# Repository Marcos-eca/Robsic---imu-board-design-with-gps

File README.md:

# Módulo GPS-IMU.

## Representação 2d e 3d da placa

## Elementos principais para a confecção da placa:

* GPS e IMU - OpenIMU300ZI.
* Esquematico do regulador de tensão fornecido pelo texas instruments no datasheet do LM1117.

## Connector e tabela de informações sobre a função de cada pino do IMU.

## Informações sobre a alimentação, conexão das portas seriais e o seletor de interface (pin_7 - comunicação UART/SPI).

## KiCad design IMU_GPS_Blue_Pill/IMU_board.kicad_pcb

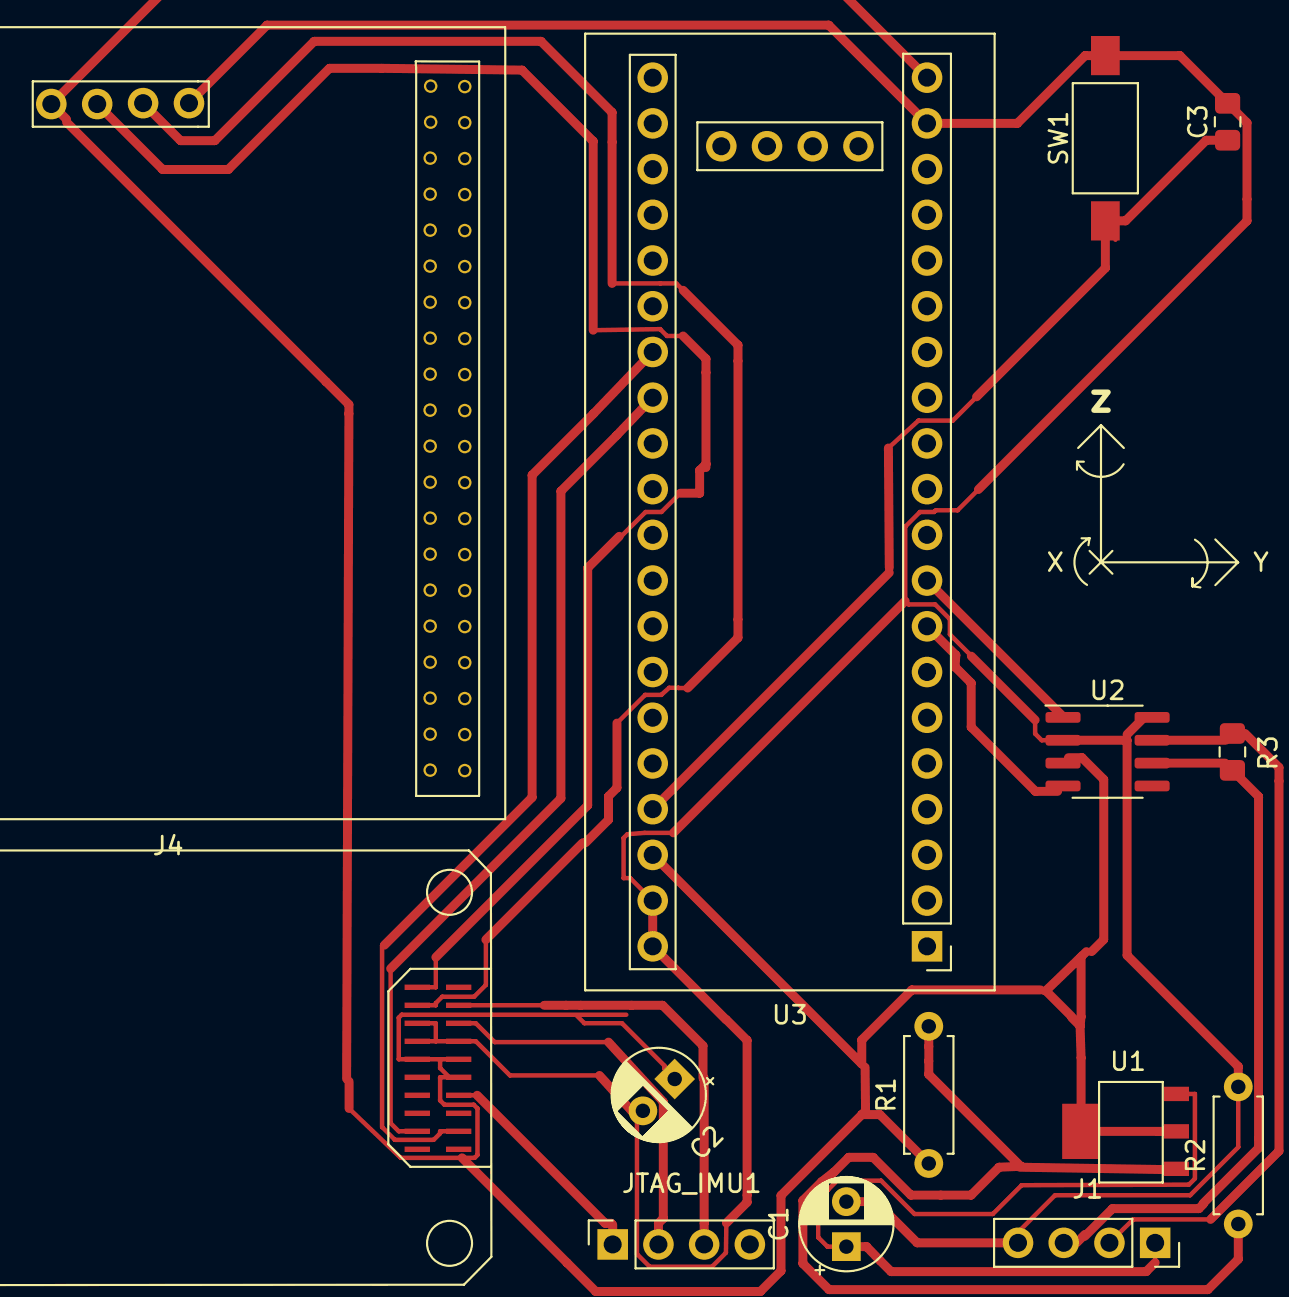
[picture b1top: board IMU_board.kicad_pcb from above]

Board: 4 copper layers, 14 parts (0 on the bottom side), 16 nets.

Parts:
C1: 10uF; CP_Radial_D5.0mm_P2.50mm
C2: 100uF; CP_Radial_D5.0mm_P2.50mm
C3: c_100n; C_0805_2012Metric_Pad1.15x1.40mm_HandSolder
J1: Conn_01x04; PinSocket_1x04_P2.54mm_Vertical
J4: Conn_02x20_Top_Bottom; conn_gps_female_2x20
J5: Conn_02x10_Odd_Even; imu_connector_female_2x10
JTAG_IMU1: Conn_01x04; PinSocket_1x04_P2.54mm_Vertical
R1: 1k; R_Axial_DIN0207_L6.3mm_D2.5mm_P7.62mm_Horizontal
R2: 620 Ohm; R_Axial_DIN0207_L6.3mm_D2.5mm_P7.62mm_Horizontal
R3: r_120; R_0805_2012Metric_Pad1.15x1.40mm_HandSolder
SW1: sw_FSMSM; SW_SPST_FSMSM
U1: LM1117-3.3; LM1117IMP_3.3_NOPB
U2: u_SN65HVD230; SOIC-8_3.9x4.9mm_P1.27mm
U3: YAAJ_BluePill_Part_Like_SWD_Breakout; YAAJ_BluePill_SWD_2

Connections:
+3V3: C2.1, J4.22, J5.10, J5.11, J5.12, R1.1, U1.2, U2.3, U3.20, U3.38
/IMU/nrst_imu: J5.8, JTAG_IMU1.1
/IMU/swclk_imu: J5.18, JTAG_IMU1.3
/IMU/swdio_imu: J5.16, JTAG_IMU1.2
/IMU/uart2_rx_in_gps: J4.15, J5.19
/IMU/uart_rx_in_imu: J5.4, U3.27
/Sheet61C5C9E4/can_rx: U2.4, U3.8
/Sheet61C5C9E4/can_tx: U2.1, U3.9
/Sheet61C5C9E4/nrst: C3.1, SW1.1, U3.37
/Sheet61C5C9E4/uart_rx_in_imu: J5.3, U3.28
/Sheet61C7FD48/uart2_rx_in_gps: J4.35, J5.17
/canH: J1.2, R3.1, U2.7
/canL: J1.3, R3.2, U2.6
GND: C1.2, C2.2, C3.2, J1.4, J4.40, J5.13, J5.14, J5.15, R2.2, SW1.2, U2.2, U2.8, U3.19, U3.39, U3.40
unnamed: R1.2, R2.1, U1.1
vcc_12: C1.1, J1.1, U1.3

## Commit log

2022-02-19 RBS_IMU_GPS_v_
2022-02-22 datasheet_connector
2022-03-04 info
